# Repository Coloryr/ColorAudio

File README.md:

# ColorAudio

通用耳放，目前支持：
- 音乐播放
  - MP3音频解码，信息显示
  - FLAC音频解码，信息显示
- 蓝牙音频播放
  - SBC编码
  - AAC编码
  - aptx编码(freeaptx解码库)
- USB音频播放
  - UAC1 (最大96K 32bit，只能设置一种采样大小)
  - UAV2 (最大192K 32bit，支持多种采样大小)

主控RK3506，DAC：cs43198x2，运放：opa1622

linux6.1 RK的SDK

pcb目录是硬件原理图和PCB  
linux目录是RK SDK修补包  
src目录是软件程序源码

使用的其他开源代码库，直接使用代码编译  
| 名称  | 描述 | 链接 |
|---|---|---|
| Lvgl | 轻量界面框架 | [GitHub](https://github.com/lvgl/lvgl) |
| arduinoFFT | 快速傅里叶变换 | [GitHub](https://github.com/kosme/arduinoFFT) |
| nlohmann/json | json解析库 | [GitHub](https://github.com/nlohmann/json) |
| bluez-alsa | 蓝牙音频库 | [GitHub](https://github.com/arkq/bluez-alsa) |
| minimp4 | MP4文件解析 | [GitHub](https://github.com/lieff/minimp4) |
| ncmdump | ncm文件解析 | [GitHub](https://github.com/taurusxin/ncmdump) |

使用的开源库，使用链接方式  
| 名称  | 描述 | 链接 |
| libpng | png解码库 | [GitHub](https://github.com/pnggroup/libpng) |
| boost | C++库 | [boost](https://www.boost.org/) |
| flac | flac解码库 | [GitHub](https://github.com/xiph/flac) |
| libjpeg-turbo | jpeg解码库 | [GitHub](https://github.com/libjpeg-turbo/libjpeg-turbo) |
| libmad | MP3解码库 | [GitHub](https://github.com/markjeee/libmad) |
| openh264 | H264解码库 | [GitHub](https://github.com/cisco/openh264) |
| librime | 输入法 | [GitHub](https://github.com/rime/librime) |

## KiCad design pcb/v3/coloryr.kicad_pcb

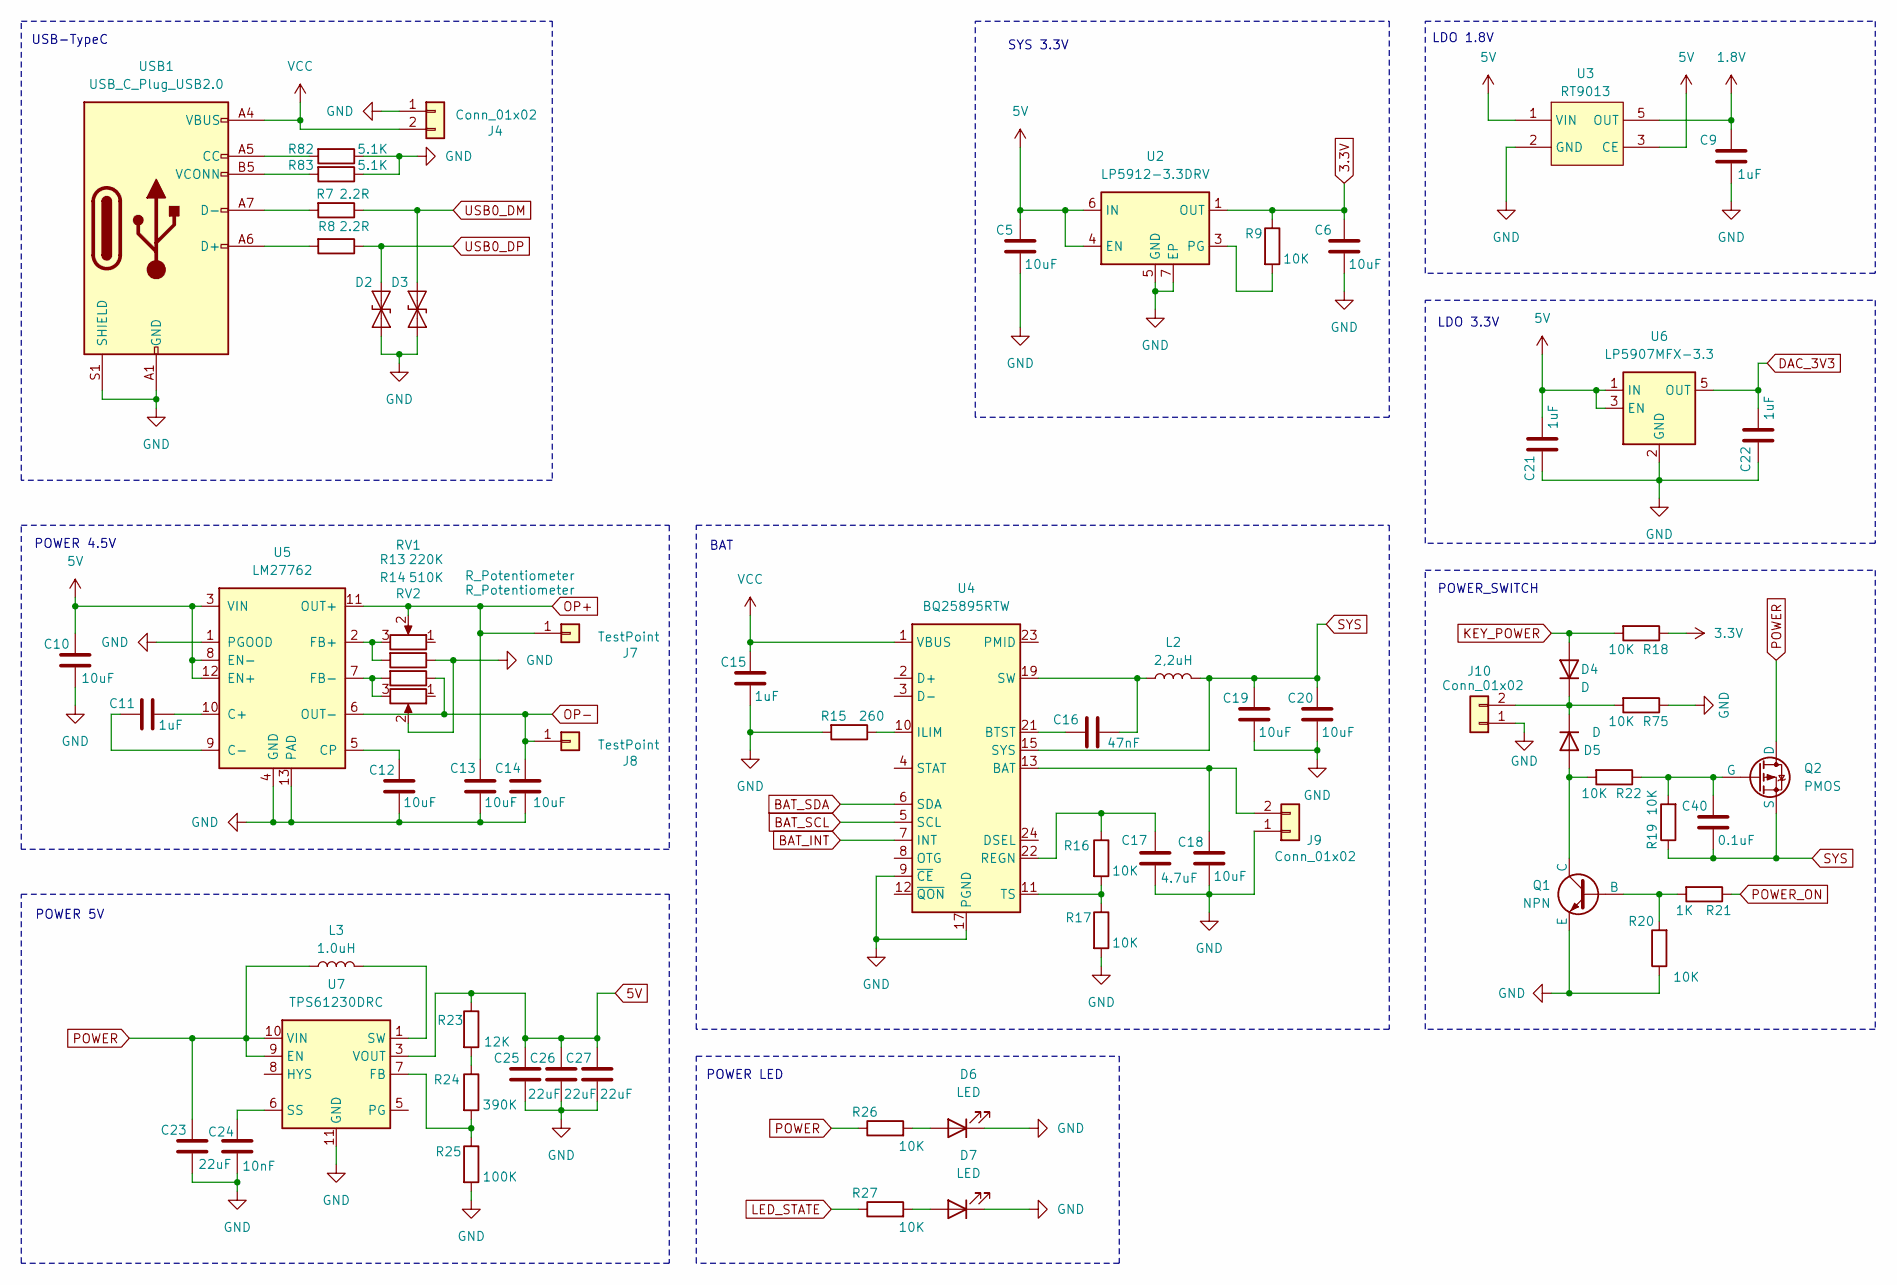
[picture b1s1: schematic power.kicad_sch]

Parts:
C5, C6, C10, C12, C13, C14, C18, C19, C20: 10uF; C_0402_1005Metric_Pad0.74x0.62mm_HandSolder
C9, C11, C15, C21, C22: 1uF; C_0402_1005Metric_Pad0.74x0.62mm_HandSolder
C16: 47nF; C_0402_1005Metric_Pad0.74x0.62mm_HandSolder
C17: 4.7uF; C_0402_1005Metric_Pad0.74x0.62mm_HandSolder
C23, C25, C26, C27: 22uF; C_0603_1608Metric_Pad1.08x0.95mm_HandSolder
C24: 10nF; C_0402_1005Metric_Pad0.74x0.62mm_HandSolder
C40: 0.1uF; C_0402_1005Metric_Pad0.74x0.62mm_HandSolder
D2, D3: ESD9B5.0ST5G; D_SOD-523
D4, D5: D; D_SOD-323_HandSoldering
D6, D7: LED; D_0402_1005Metric_Pad0.77x0.64mm_HandSolder
J4, J10: Conn_01x02; PinHeader_1x02_P2.00mm_Vertical
J7, J8: TestPoint; TestPoint_Pad_D1.0mm
J9: Conn_01x02; PinHeader_1x02_P2.54mm_Vertical
L2: 2,2uH; L_1008_2520Metric_Pad1.43x2.20mm_HandSolder
L3: 1.0uH; L_Changjiang_FXL0530
Q1: NPN; SOT-23
Q2: PMOS; SOT-23
R7, R8: 2.2R; C_0402_1005Metric_Pad0.74x0.62mm_HandSolder
R9, R16, R17, R26, R27: 10K; C_0402_1005Metric_Pad0.74x0.62mm_HandSolder
R13: 220K; C_0402_1005Metric_Pad0.74x0.62mm_HandSolder
R14: 510K; C_0402_1005Metric_Pad0.74x0.62mm_HandSolder
R15: 260; C_0402_1005Metric_Pad0.74x0.62mm_HandSolder
R18, R19, R20, R22, R75: 10K; R_0402_1005Metric_Pad0.72x0.64mm_HandSolder
R21: 1K; R_0402_1005Metric_Pad0.72x0.64mm_HandSolder
R23: 12K; C_0402_1005Metric_Pad0.74x0.62mm_HandSolder
R24: 390K; C_0402_1005Metric_Pad0.74x0.62mm_HandSolder
R25: 100K; C_0402_1005Metric_Pad0.74x0.62mm_HandSolder
R82, R83: 5.1K; C_0402_1005Metric_Pad0.74x0.62mm_HandSolder
RV1, RV2: R_Potentiometer; Potentiometer_Bourns_TC33X_Vertical
U2: LP5912-3.3DRV; WSON-6-1EP_2x2mm_P0.65mm_EP1x1.6mm_ThermalVias
U3: RT9013; SOT-23-5
U4: BQ25895RTW; Texas_RTW_WQFN-24-1EP_4x4mm_P0.5mm_EP2.7x2.7mm_ThermalVias
U5: LM27762; WSON-12-1EP_3x2mm_P0.5mm_EP1x2.65_ThermalVias
U6: LP5907MFX-3.3; SOT-23-5
U7: TPS61230DRC; Texas_S-PVSON-N10_ThermalVias
USB1: USB_C_Plug_USB2.0; USB_C_Receptacle_GCT_USB4105-xx-A_16P_TopMnt_Horizontal

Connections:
1.8V: C9.1, U3.5 (OUT); also elsewhere on the board
3.3V: C6.1, R9.1, R18.1, U2.1 (OUT); also elsewhere on the board
5V: C5.1, C10.1, C21.1, C25.1, C26.1, C27.1, R23.1, U2.4 (EN), U2.6 (IN), U3.1 (VIN), U3.3 (CE), U5.3 (VIN), U5.8 (EN-), U5.12 (EN+), U6.1 (IN), U6.3 (EN), U7.3 (VOUT), U7.4 (VOUT); also elsewhere on the board
BAT_INT: U4.7 (INT); also elsewhere on the board
BAT_SCL: U4.5 (SCL); also elsewhere on the board
BAT_SDA: U4.6 (SDA); also elsewhere on the board
DAC_3V3: C22.1, U6.5 (OUT); also elsewhere on the board
GND: C5.2, C6.2, C9.2, C10.2, C12.1, C13.1, C14.1, C15.2, C17.1, C18.2, C19.2, C20.2, C21.2, C22.2, C23.2, C24.1, C25.2, C26.2, C27.2, D2.1 (A1), D3.1 (A1), D6.1 (K), D7.1 (K), J4.1, J9.1, J10.1, Q1.3 (E), R13.1, R15.2, R17.2, R20.1, R25.2, R75.1, R82.1, R83.1, RV2.2, U2.5 (GND), U2.7 (EP), U3.2 (GND), U4.9 (~CE), U4.17 (PGND), U4.18 (PGND), U4.25 (PGND), U5.1 (PGOOD), U5.4 (GND), U5.13 (PAD), U6.2 (GND), U7.11 (GND), USB1.A1 (GND), USB1.A12 (GND), USB1.B1 (GND), USB1.B12 (GND), USB1.S1 (SHIELD); also elsewhere on the board
KEY_POWER: D4.2 (A), R18.2; also elsewhere on the board
LED_STATE: R27.1; also elsewhere on the board
unnamed: C16.2, L2.1, U4.19 (SW), U4.20 (SW)
unnamed: D4.1 (K), D5.1 (K), J10.2, R75.2
unnamed: D5.2 (A), Q1.1 (C), R22.2
unnamed: D6.2 (A), R26.2
unnamed: D7.2 (A), R27.2
unnamed: C18.1, J9.2, U4.13 (BAT), U4.14 (BAT)
unnamed: L3.2, U7.1 (SW), U7.2 (SW)
unnamed: Q1.2 (B), R20.2, R21.2
unnamed: C40.1, Q2.2 (G), R19.2, R22.1
unnamed: R7.2, USB1.A7 (D-), USB1.B7 (D-)
unnamed: R8.2, USB1.A6 (D+), USB1.B6 (D+)
unnamed: R23.2, R24.1
unnamed: R9.2, U2.3 (PG)
unnamed: C16.1, U4.21 (BTST)
unnamed: R15.1, U4.10 (ILIM)
unnamed: C17.2, R16.1, U4.22 (REGN)
unnamed: R16.2, R17.1, U4.11 (TS)
unnamed: C11.2, U5.10 (C+)
unnamed: C11.1, U5.9 (C-)
unnamed: C12.2, U5.5 (CP)
unnamed: R13.2, RV1.3, U5.2 (FB+)
unnamed: R14.2, RV2.3, U5.7 (FB-)
unnamed: R24.2, R25.1, U7.7 (FB)
unnamed: C24.2, U7.6 (SS)
unnamed: R82.2, USB1.A5 (CC)
unnamed: R83.2, USB1.B5 (VCONN)
OP+: C13.2, J7.1, RV1.2, U5.11 (OUT+); also elsewhere on the board
OP-: C14.2, J8.1, R14.1, U5.6 (OUT-); also elsewhere on the board
POWER: C23.1, L3.1, Q2.1 (D), R26.1, U7.9 (EN), U7.10 (VIN)
POWER_ON: R21.1; also elsewhere on the board
SYS: C19.1, C20.1, C40.2, L2.2, Q2.3 (S), R19.1, U4.15 (SYS), U4.16 (SYS)
USB0_DM: D3.2 (A2), R7.1; also elsewhere on the board
USB0_DP: D2.2 (A2), R8.1; also elsewhere on the board
VCC: C15.1, J4.2, U4.1 (VBUS), USB1.A4 (VBUS), USB1.A9 (VBUS), USB1.B4 (VBUS), USB1.B9 (VBUS); also elsewhere on the board

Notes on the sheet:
POWER LED
BAT
LDO 3.3V
POWER_SWITCH
LDO 1.8V
SYS 3.3V
POWER 4.5V
USB-TypeC
POWER 5V

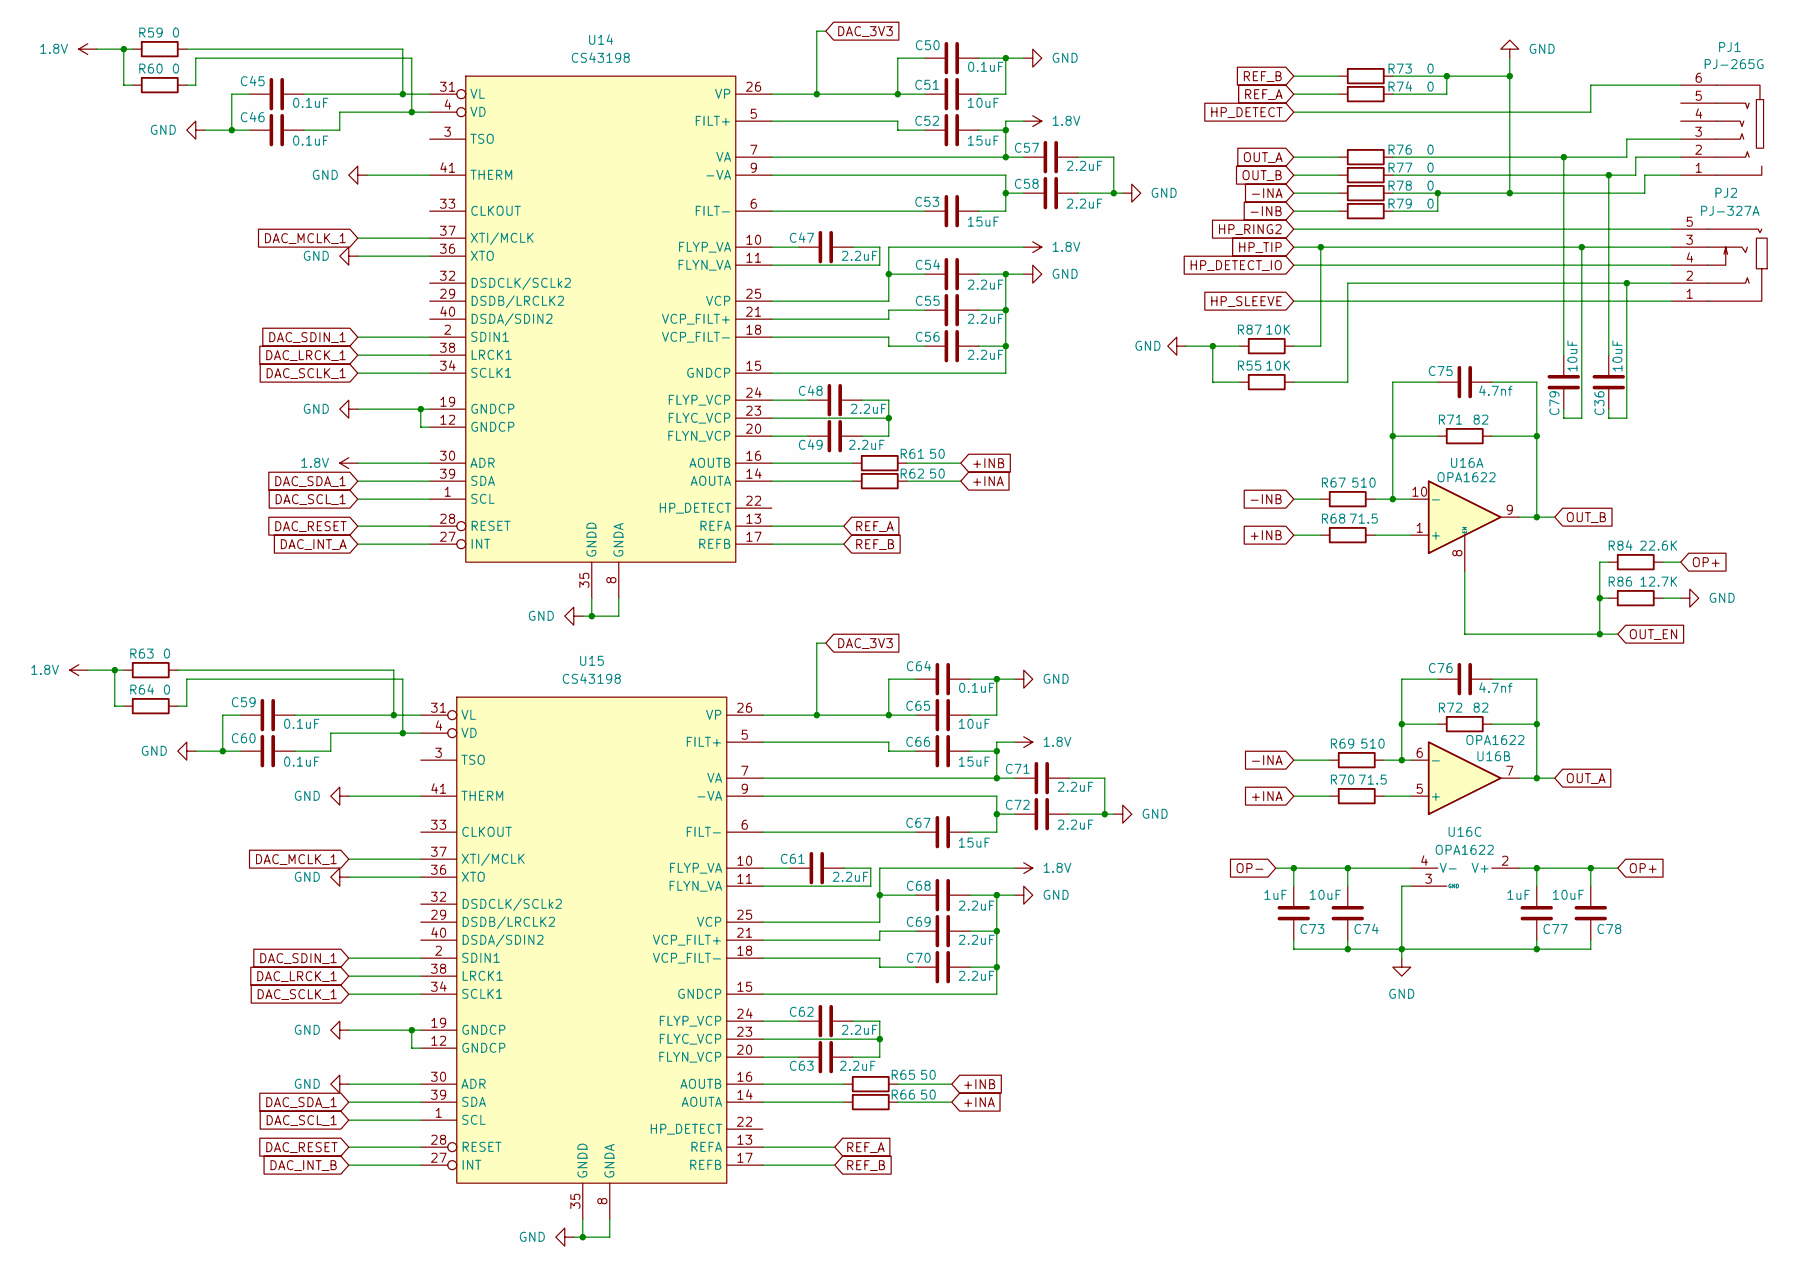
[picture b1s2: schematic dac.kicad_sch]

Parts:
C36, C79: 10uF; C_0603_1608Metric_Pad1.08x0.95mm_HandSolder
C45, C46, C50, C59, C60, C64: 0.1uF; C_0402_1005Metric_Pad0.74x0.62mm_HandSolder
C47, C48, C49, C54, C55, C56, C57, C58, C61, C62, C63, C68, C69, C70, C71, C72: 2.2uF; C_0402_1005Metric_Pad0.74x0.62mm_HandSolder
C51, C65, C74, C78: 10uF; C_0402_1005Metric_Pad0.74x0.62mm_HandSolder
C52, C53, C66, C67: 15uF; C_0402_1005Metric_Pad0.74x0.62mm_HandSolder
C73, C77: 1uF; C_0402_1005Metric_Pad0.74x0.62mm_HandSolder
C75, C76: 4.7nf; C_0805_2012Metric_Pad1.18x1.45mm_HandSolder
PJ1: PJ-265G; PinHeader_1x06_P2.54mm_Vertical
PJ2: PJ-327A; PinHeader_1x05_P2.54mm_Vertical; Manufacturer Part PJ-327A; LCSC Part Name 3.5mm耳机座
R55, R87: 10K; C_0402_1005Metric_Pad0.74x0.62mm_HandSolder
R59, R60, R63, R64: 0; R_0402_1005Metric_Pad0.72x0.64mm_HandSolder
R61, R62, R65, R66: 50; R_0805_2012Metric
R67, R69: 510; R_0805_2012Metric
R68, R70: 71.5; R_0805_2012Metric
R71, R72: 82; R_0805_2012Metric
R73, R74, R76, R77, R78, R79: 0; R_0805_2012Metric
R84: 22.6K; C_0402_1005Metric_Pad0.74x0.62mm_HandSolder
R86: 12.7K; C_0402_1005Metric_Pad0.74x0.62mm_HandSolder
U14, U15: CS43198; QFN-40-1EP_5x5mm_P0.4mm_EP3.6x3.6mm_ThermalVias
U16: OPA1622; Texas_S-PVSON-N10

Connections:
1.8V: C52.2, C54.2, C57.2, C66.2, C68.2, C71.2, R59.2, R60.2, R63.2, R64.2, U14.7 (VA), U14.25 (VCP), U14.30 (ADR), U15.7 (VA), U15.25 (VCP); also elsewhere on the board
+INA: R62.1, R66.1, R70.2
+INB: R61.1, R65.1, R68.2
-INA: R69.2, R78.2
-INB: R67.2, R79.2
DAC_3V3: C50.2, C51.1, C64.2, C65.1, U14.26 (VP), U15.26 (VP); also elsewhere on the board
DAC_INT_A: U14.27 (INT); also elsewhere on the board
DAC_INT_B: U15.27 (INT); also elsewhere on the board
DAC_LRCK_1: U14.38 (LRCK1), U15.38 (LRCK1); also elsewhere on the board
DAC_MCLK_1: U14.37 (XTI/MCLK), U15.37 (XTI/MCLK); also elsewhere on the board
DAC_RESET: U14.28 (RESET), U15.28 (RESET); also elsewhere on the board
DAC_SCLK_1: U14.34 (SCLK1), U15.34 (SCLK1); also elsewhere on the board
DAC_SCL_1: U14.1 (SCL), U15.1 (SCL); also elsewhere on the board
DAC_SDA_1: U14.39 (SDA), U15.39 (SDA); also elsewhere on the board
DAC_SDIN_1: U14.2 (SDIN1), U15.2 (SDIN1); also elsewhere on the board
GND: C45.2, C46.2, C50.1, C51.2, C54.1, C55.1, C56.1, C57.1, C58.1, C59.2, C60.2, C64.1, C65.2, C68.1, C69.1, C70.1, C71.1, C72.1, C73.1, C74.1, C77.1, C78.1, PJ1.1, R55.2, R73.1, R74.1, R78.1, R79.1, R86.1, R87.2, U14.8 (GNDA), U14.12 (GNDCP), U14.15 (GNDCP), U14.19 (GNDCP), U14.35 (GNDD), U14.36 (XTO), U14.41 (THERM), U15.8 (GNDA), U15.12 (GNDCP), U15.15 (GNDCP), U15.19 (GNDCP), U15.30 (ADR), U15.35 (GNDD), U15.36 (XTO), U15.41 (THERM), U16.3 (GND); also elsewhere on the board
HP_DETECT: PJ1.6; also elsewhere on the board
HP_DETECT_IO: PJ2.4; also elsewhere on the board
HP_RING2: PJ2.5; also elsewhere on the board
HP_SLEEVE: PJ2.1; also elsewhere on the board
HP_TIP: C79.1, PJ2.3, R87.1; also elsewhere on the board
unnamed: C36.1, PJ2.2, R55.1
unnamed: C36.2, PJ1.2, R77.1
unnamed: C79.2, PJ1.3, R76.1
unnamed: C53.2, C58.2, U14.9 (-VA)
unnamed: R62.2, U14.14 (AOUTA)
unnamed: R61.2, U14.16 (AOUTB)
unnamed: C52.1, U14.5 (FILT+)
unnamed: C53.1, U14.6 (FILT-)
unnamed: C48.1, C49.1, U14.23 (FLYC_VCP)
unnamed: C47.1, U14.11 (FLYN_VA)
unnamed: C49.2, U14.20 (FLYN_VCP)
unnamed: C47.2, U14.10 (FLYP_VA)
unnamed: C48.2, U14.24 (FLYP_VCP)
unnamed: C55.2, U14.21 (VCP_FILT+)
unnamed: C56.2, U14.18 (VCP_FILT-)
unnamed: C46.1, R60.1, U14.4 (VD)
unnamed: C45.1, R59.1, U14.31 (VL)
unnamed: C67.2, C72.2, U15.9 (-VA)
unnamed: R66.2, U15.14 (AOUTA)
unnamed: R65.2, U15.16 (AOUTB)
unnamed: C66.1, U15.5 (FILT+)
unnamed: C67.1, U15.6 (FILT-)
unnamed: C62.1, C63.1, U15.23 (FLYC_VCP)
unnamed: C61.1, U15.11 (FLYN_VA)
unnamed: C63.2, U15.20 (FLYN_VCP)
unnamed: C61.2, U15.10 (FLYP_VA)
unnamed: C62.2, U15.24 (FLYP_VCP)
unnamed: C69.2, U15.21 (VCP_FILT+)
unnamed: C70.2, U15.18 (VCP_FILT-)
unnamed: C60.1, R64.1, U15.4 (VD)
unnamed: C59.1, R63.1, U15.31 (VL)
unnamed: R68.1, U16.1 (+)
unnamed: C75.2, R67.1, R71.2, U16.10 (-)
unnamed: R70.1, U16.5 (+)
unnamed: C76.2, R69.1, R72.2, U16.6 (-)
OP+: C77.2, C78.2, R84.1, U16.2 (V+); also elsewhere on the board
OP-: C73.2, C74.2, U16.4 (V-), U16.11 (V-); also elsewhere on the board
OUT_A: C76.1, R72.1, R76.2, U16.7
OUT_B: C75.1, R71.1, R77.2, U16.9
OUT_EN: R84.2, R86.2, U16.8 (EN); also elsewhere on the board
REF_A: R74.2, U14.13 (REFA), U15.13 (REFA)
REF_B: R73.2, U14.17 (REFB), U15.17 (REFB)

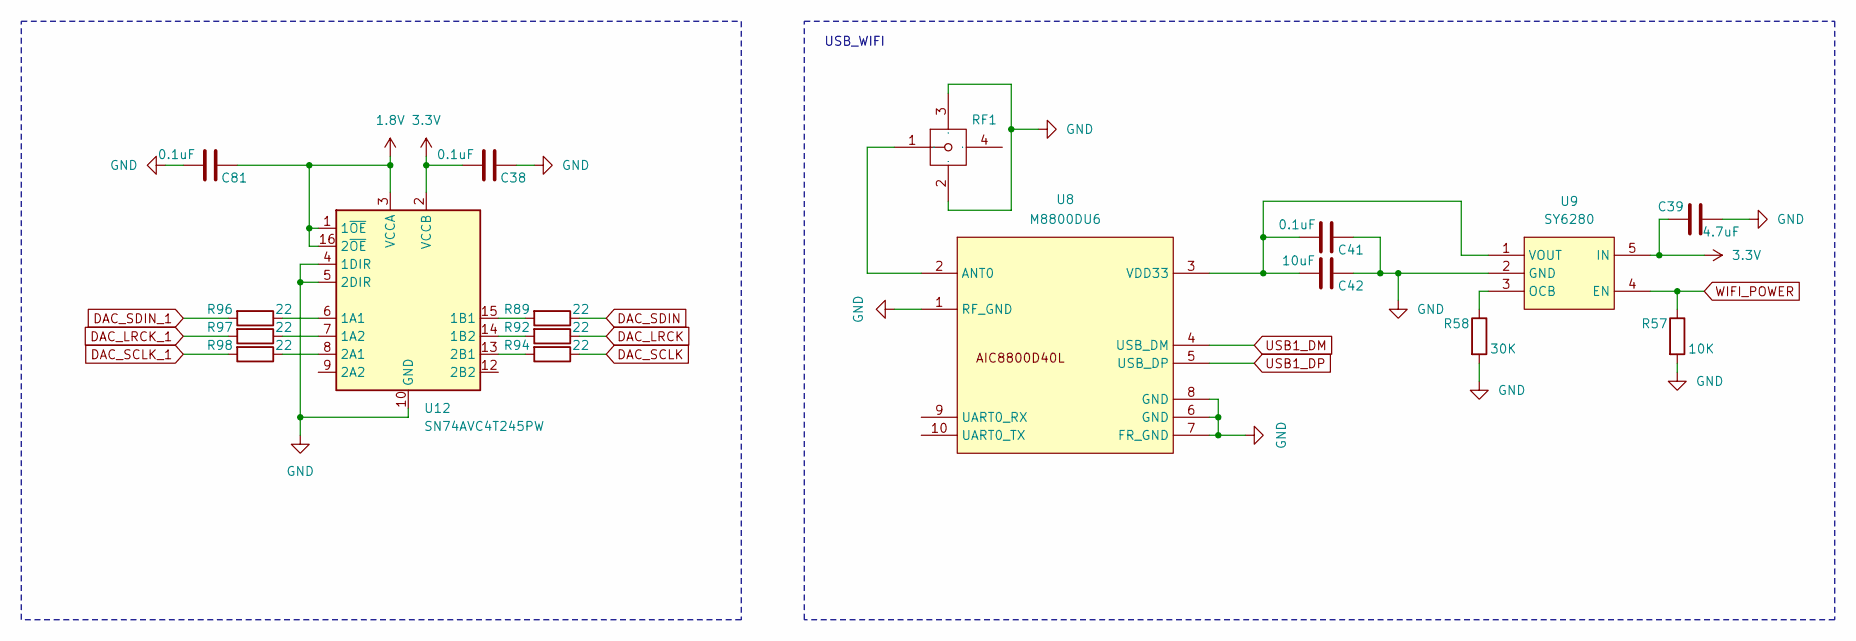
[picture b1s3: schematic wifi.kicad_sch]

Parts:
C38, C41, C81: 0.1uF; C_0402_1005Metric_Pad0.74x0.62mm_HandSolder
C39: 4.7uF; C_0402_1005Metric_Pad0.74x0.62mm_HandSolder
C42: 10uF; C_0402_1005Metric_Pad0.74x0.62mm_HandSolder
R57: 10K; C_0402_1005Metric_Pad0.74x0.62mm_HandSolder
R58: 30K; C_0402_1005Metric_Pad0.74x0.62mm_HandSolder
R89, R92, R94, R96, R97, R98: 22; C_0402_1005Metric_Pad0.74x0.62mm_HandSolder
RF1: 6GHz; IPEX-SMD_BWIPX-3-001E-1; Manufacturer Part BWIPX-3-001E; LCSC Part Name IPEX 内针
U8: M8800DU6; BL_M8800DU6_40L
U9: SY6280; SOT-23-5
U12: SN74AVC4T245PW; UQFN-16_1.8x2.6mm_P0.4mm

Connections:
1.8V: C81.2, U12.1 (1~OE), U12.3 (VCCA), U12.16 (2~OE); also elsewhere on the board
3.3V: C38.1, C39.1, U9.5 (IN), U12.2 (VCCB); also elsewhere on the board
DAC_LRCK: R92.1; also elsewhere on the board
DAC_LRCK_1: R97.2; also elsewhere on the board
DAC_SCLK: R94.1; also elsewhere on the board
DAC_SCLK_1: R98.2; also elsewhere on the board
DAC_SDIN: R89.1; also elsewhere on the board
DAC_SDIN_1: R96.2; also elsewhere on the board
GND: C38.2, C39.2, C41.1, C42.1, C81.1, R57.2, R58.2, RF1.2, RF1.3, U8.1 (RF_GND), U8.6 (GND), U8.7 (FR_GND), U8.8 (GND), U9.2 (GND), U12.4 (1DIR), U12.5 (2DIR), U12.10 (GND), U12.11 (GND); also elsewhere on the board
unnamed: RF1.1, U8.2 (ANT0)
unnamed: C41.2, C42.2, U8.3 (VDD33), U9.1 (VOUT)
unnamed: R58.1, U9.3 (OCB)
unnamed: R96.1, U12.6 (1A1)
unnamed: R97.1, U12.7 (1A2)
unnamed: R89.2, U12.15 (1B1)
unnamed: R92.2, U12.14 (1B2)
unnamed: R98.1, U12.8 (2A1)
unnamed: R94.2, U12.13 (2B1)
USB1_DM: U8.4 (USB_DM); also elsewhere on the board
USB1_DP: U8.5 (USB_DP); also elsewhere on the board
WIFI_POWER: R57.1, U9.4 (EN); also elsewhere on the board

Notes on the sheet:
USB_WIFI

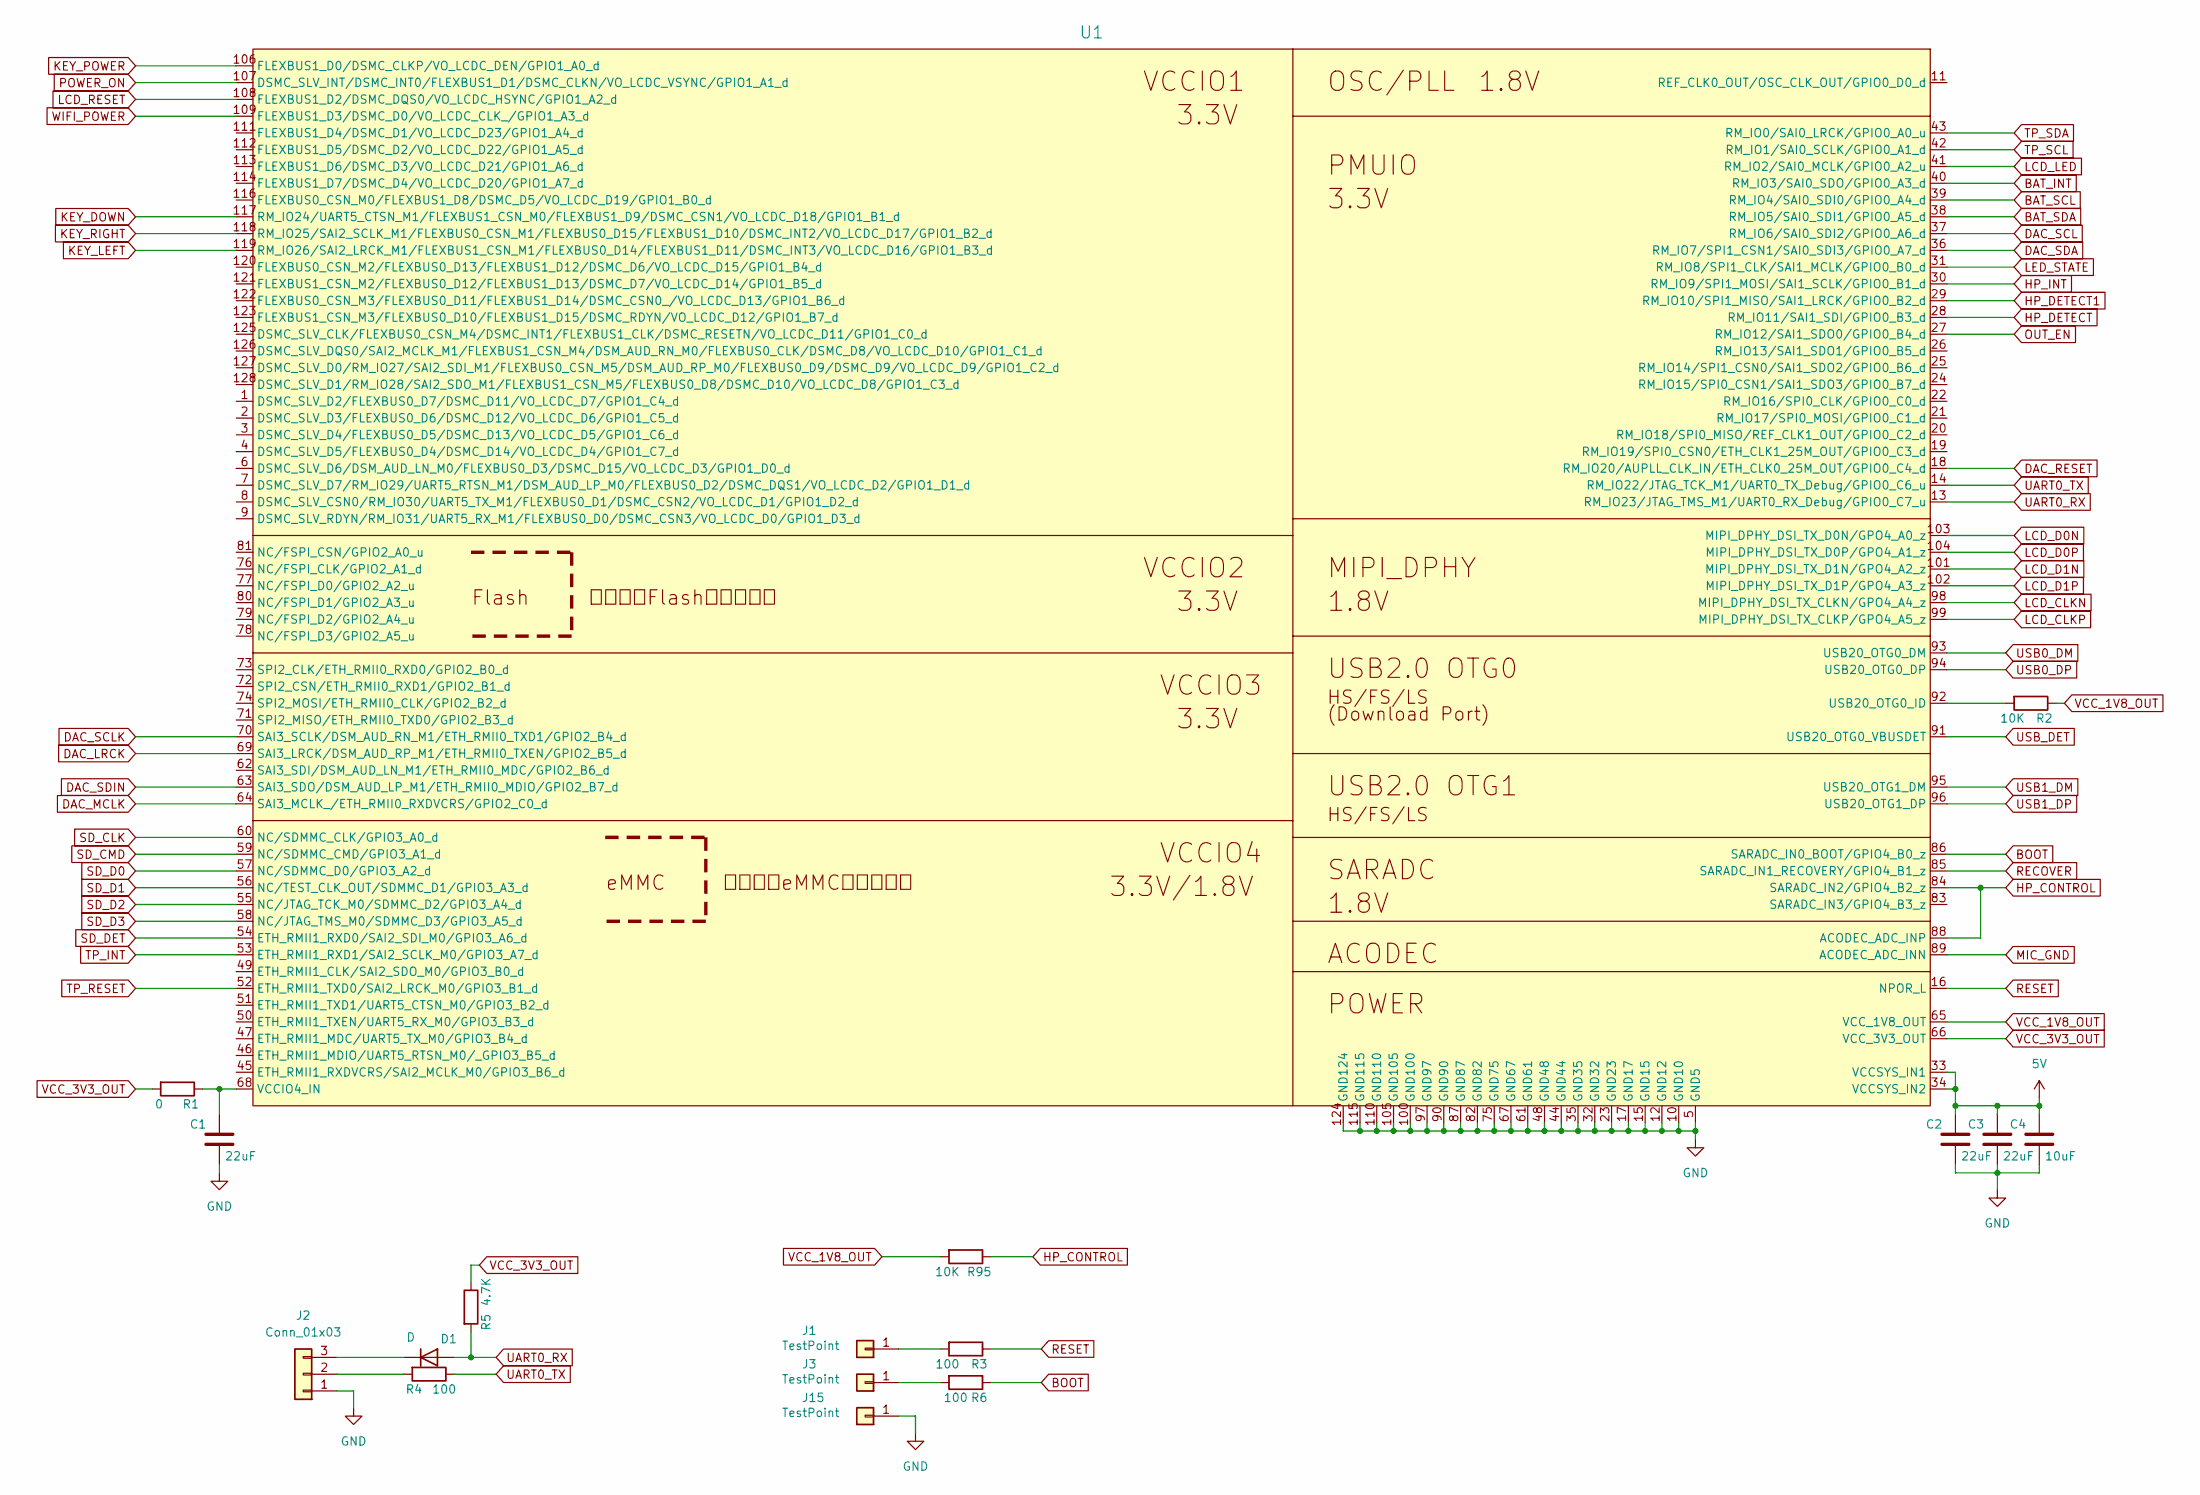
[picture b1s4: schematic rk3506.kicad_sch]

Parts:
C1, C2, C3: 22uF; C_0603_1608Metric_Pad1.08x0.95mm_HandSolder
C4: 10uF; C_0402_1005Metric_Pad0.74x0.62mm_HandSolder
D1: D; D_SOD-323_HandSoldering
J1, J3, J15: TestPoint; TestPoint_Pad_D1.0mm
J2: Conn_01x03; PinHeader_1x03_P1.27mm_Vertical
R1: 0; R_0402_1005Metric_Pad0.72x0.64mm_HandSolder
R2, R95: 10K; R_0402_1005Metric_Pad0.72x0.64mm_HandSolder
R3, R4, R6: 100; R_0402_1005Metric_Pad0.72x0.64mm_HandSolder
R5: 4.7K; R_0402_1005Metric_Pad0.72x0.64mm_HandSolder
U1: SOM3562_18; rk3506

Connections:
5V: C2.1, C3.1, C4.1, U1.33 (VCCSYS_IN1), U1.34 (VCCSYS_IN2); also elsewhere on the board
BAT_INT: U1.40 (RM_IO3/SAI0_SDO/GPIO0_A3_d); also elsewhere on the board
BAT_SCL: U1.39 (RM_IO4/SAI0_SDI0/GPIO0_A4_d); also elsewhere on the board
BAT_SDA: U1.38 (RM_IO5/SAI0_SDI1/GPIO0_A5_d); also elsewhere on the board
BOOT: R6.1, U1.86 (SARADC_IN0_BOOT/GPIO4_B0_z)
DAC_INT_A: U1.47 (ETH_RMII1_MDC/UART5_TX_M0/GPIO3_B4_d); also elsewhere on the board
DAC_INT_B: U1.46 (ETH_RMII1_MDIO/UART5_RTSN_M0/_GPIO3_B5_d); also elsewhere on the board
DAC_LRCK: U1.69 (SAI3_LRCK/DSM_AUD_RP_M1/ETH_RMII0_TXEN/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); also elsewhere on the board
DAC_MCLK: U1.64 (SAI3_MCLK_/ETH_RMII0_RXDVCRS/GPIO2_C0_d); also elsewhere on the board
DAC_RESET: U1.18 (RM_IO20/AUPLL_CLK_IN/ETH_CLK0_25M_OUT/G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); also elsewhere on the board
DAC_SCL: U1.37 (RM_IO6/SAI0_SDI2/GPIO0_A6_d); also elsewhere on the board
DAC_SCLK: U1.70 (SAI3_SCLK/DSM_AUD_RN_M1/ETH_RMII0_TXD1/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); also elsewhere on the board
DAC_SDA: U1.36 (RM_IO7/SPI1_CSN1/SAI0_SDI3/GPIO0_A7_d); also elsewhere on the board
DAC_SDIN: U1.63 (SAI3_SDO/DSM_AUD_LP_M1/ETH_RMII0_MDIO/G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); also elsewhere on the board
GND: C1.2, C2.2, C3.2, C4.2, J2.1, J15.1, U1.5 (GND5), U1.10 (GND10), U1.12 (GND12), U1.15 (GND15), U1.17 (GND17), U1.23 (GND23), U1.32 (GND32), U1.35 (GND35), U1.44 (GND44), U1.48 (GND48), U1.61 (GND61), U1.67 (GND67), U1.75 (GND75), U1.82 (GND82), U1.87 (GND87), U1.90 (GND90), U1.97 (GND97), U1.100 (GND100), U1.105 (GND105), U1.110 (GND110), U1.115 (GND115), U1.124 (GND124); also elsewhere on the board
HP_CONTROL: R95.1, U1.84 (SARADC_IN2/GPIO4_B2_z), U1.88 (ACODEC_ADC_INP); also elsewhere on the board
HP_DETECT: U1.28 (RM_IO11/SAI1_SDI/GPIO0_B3_d); also elsewhere on the board
HP_DETECT1: U1.29 (RM_IO10/SPI1_MISO/SAI1_LRCK/GPIO0_B2_d); also elsewhere on the board
HP_INT: U1.30 (RM_IO9/SPI1_MOSI/SAI1_SCLK/GPIO0_B1_d); also elsewhere on the board
KEY_DOWN: U1.117 (RM_IO24/UART5_CTSN_M1/FLEXBUS1_CSN_M0/F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); also elsewhere on the board
KEY_LEFT: U1.119 (RM_IO26/SAI2_LRCK_M1/FLEXBUS1_CSN_M1/FL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); also elsewhere on the board
KEY_POWER: U1.106 (FLEXBUS1_D0/DSMC_CLKP/VO_LCDC_DEN/GPIO1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); also elsewhere on the board
KEY_RIGHT: U1.118 (RM_IO25/SAI2_SCLK_M1/FLEXBUS0_CSN_M1/FL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); also elsewhere on the board
LCD_CLKN: U1.98 (MIPI_DPHY_DSI_TX_CLKN/GPO4_A4_z); also elsewhere on the board
LCD_CLKP: U1.99 (MIPI_DPHY_DSI_TX_CLKP/GPO4_A5_z); also elsewhere on the board
LCD_D0N: U1.103 (MIPI_DPHY_DSI_TX_D0N/GPO4_A0_z); also elsewhere on the board
LCD_D0P: U1.104 (MIPI_DPHY_DSI_TX_D0P/GPO4_A1_z); also elsewhere on the board
LCD_D1N: U1.101 (MIPI_DPHY_DSI_TX_D1N/GPO4_A2_z); also elsewhere on the board
LCD_D1P: U1.102 (MIPI_DPHY_DSI_TX_D1P/GPO4_A3_z); also elsewhere on the board
LCD_LED: U1.41 (RM_IO2/SAI0_MCLK/GPIO0_A2_u); also elsewhere on the board
LCD_RESET: U1.108 (FLEXBUS1_D2/DSMC_DQS0/VO_LCDC_HSYNC/GPI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); also elsewhere on the board
LED_STATE: U1.31 (RM_IO8/SPI1_CLK/SAI1_MCLK/GPIO0_B0_d); also elsewhere on the board
MIC_GND: U1.89 (ACODEC_ADC_INN); also elsewhere on the board
unnamed: D1.1 (K), J2.3
unnamed: J1.1, R3.2
unnamed: J2.2, R4.2
unnamed: J3.1, R6.2
unnamed: R2.2, U1.92 (USB20_OTG0_ID)
unnamed: C1.1, R1.1, U1.68 (VCCIO4_IN)
OUT_EN: U1.27 (RM_IO12/SAI1_SDO0/GPIO0_B4_d); also elsewhere on the board
POWER_ON: U1.107 (DSMC_SLV_INT/DSMC_INT0/FLEXBUS1_D1/DSMC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); also elsewhere on the board
RECOVER: U1.85 (SARADC_IN1_RECOVERY/GPIO4_B1_z); also elsewhere on the board
RESET: R3.1, U1.16 (NPOR_L)
SD_CLK: U1.60 (NC/SDMMC_CLK/GPIO3_A0_d); also elsewhere on the board
SD_CMD: U1.59 (NC/SDMMC_CMD/GPIO3_A1_d); also elsewhere on the board
SD_D0: U1.57 (NC/SDMMC_D0/GPIO3_A2_d); also elsewhere on the board
SD_D1: U1.56 (NC/TEST_CLK_OUT/SDMMC_D1/GPIO3_A3_d); also elsewhere on the board
SD_D2: U1.55 (NC/JTAG_TCK_M0/SDMMC_D2/GPIO3_A4_d); also elsewhere on the board
SD_D3: U1.58 (NC/JTAG_TMS_M0/SDMMC_D3/GPIO3_A5_d); also elsewhere on the board
SD_DET: U1.54 (ETH_RMII1_RXD0/SAI2_SDI_M0/GPIO3_A6_d); also elsewhere on the board
TP_INT: U1.53 (ETH_RMII1_RXD1/SAI2_SCLK_M0/GPIO3_A7_d); also elsewhere on the board
TP_RESET: U1.52 (ETH_RMII1_TXD0/SAI2_LRCK_M0/GPIO3_B1_d); also elsewhere on the board
TP_SCL: U1.42 (RM_IO1/SAI0_SCLK/GPIO0_A1_d); also elsewhere on the board
TP_SDA: U1.43 (RM_IO0/SAI0_LRCK/GPIO0_A0_u); also elsewhere on the board
UART0_RX: D1.2 (A), R5.2, U1.13 (RM_IO23/JTAG_TMS_M1/UART0_RX_Debug/GPIO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)
UART0_TX: R4.1, U1.14 (RM_IO22/JTAG_TCK_M1/UART0_TX_Debug/GPIO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)
USB0_DM: U1.93 (USB20_OTG0_DM); also elsewhere on the board
USB0_DP: U1.94 (USB20_OTG0_DP); also elsewhere on the board
USB1_DM: U1.95 (USB20_OTG1_DM); also elsewhere on the board
USB1_DP: U1.96 (USB20_OTG1_DP); also elsewhere on the board
USB_DET: U1.91 (USB20_OTG0_VBUSDET); also elsewhere on the board
VCC_1V8_OUT: R2.1, R95.2, U1.65 (VCC_1V8_OUT); also elsewhere on the board
VCC_3V3_OUT: R1.2, R5.1, U1.66 (VCC_3V3_OUT)
WIFI_POWER: U1.109 (FLEXBUS1_D3/DSMC_D0/VO_LCDC_CLK_/GPIO1_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); also elsewhere on the board

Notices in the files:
linux/out/dts/sun8i-t113s-coloraudio.dtsi:
Copyright (C) 2021-2022 Samuel Holland <samuel@sholland.org>
linux/over-v2/kernel-6.1/arch/arm/boot/dts/coloraudio-rk3506-v2-rgb-nand.dts:
Copyright (c) 2024 Rockchip Electronics Co., Ltd.
